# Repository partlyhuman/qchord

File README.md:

# Suzuki QChord Projects

Things that work with the Suzuki QChord, primarily a reproduction QCard that can be built with completely off-the-shelf parts. These projects are under active development.

# Physical devices

## [Q-Card Multicart QMC-001](pcbs/qcard-multicart)

You can get one as long as stock lasts <a href="https://ko-fi.com/s/ca15ec594a">at my Ko-Fi shop!</a>
<br>

A single cartridge that contains the entire Q-Card library, selectable by dip switches. The flash should be programmed prior to assembly, by concatenating the 4Mbit dumps you can find on archive.org.

## [Single Q-Card Reproduction](pcbs/qcard-single)

A rewriteable reproduction QCard PCB using SMD components. The flash module uses a TSOP32 package. It can be reprogrammed after assembly with the programmer adapter below.

# [Documentation](docs/)

Including 

* my research notes on the Q-Card hardware & connector
* my reverse-engineered Q-Card format
* continuing research into the sound bank present on Q-Chord

# [Software](software/)

Primarily, the `qcard` command-line tool that can be used to convert MIDI to and from Q-Cards.

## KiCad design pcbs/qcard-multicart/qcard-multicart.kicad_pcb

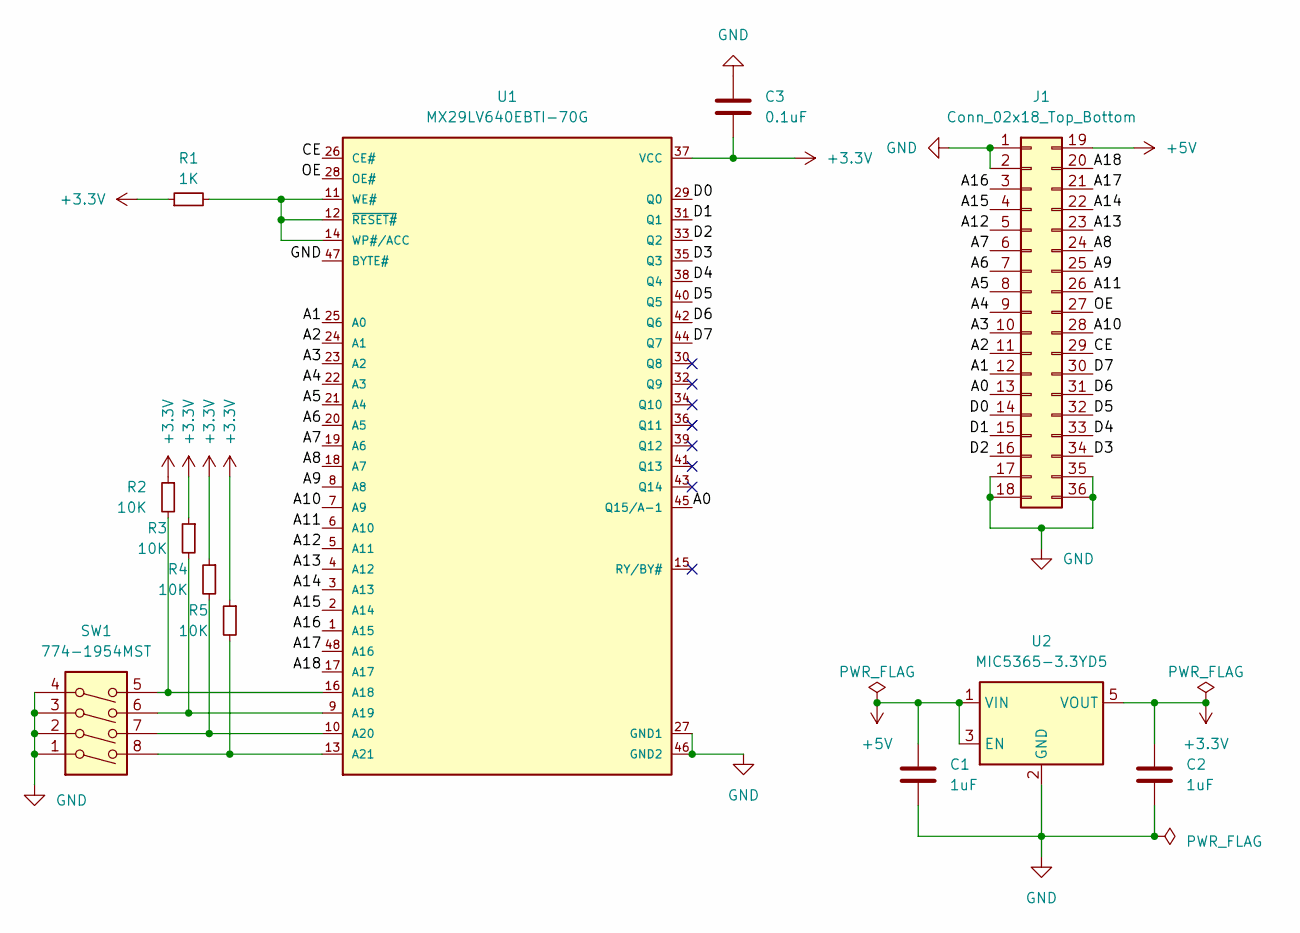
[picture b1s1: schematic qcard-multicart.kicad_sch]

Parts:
C1, C2: 1uF; C_0805_2012Metric_Pad1.18x1.45mm_HandSolder
C3: 0.1uF; C_0805_2012Metric_Pad1.18x1.45mm_HandSolder
J1: Conn_02x18_Top_Bottom; REB_EdgeConnector_36pin
R1: 1K; R_0805_2012Metric_Pad1.20x1.40mm_HandSolder
R2, R3, R4, R5: 10K; R_0805_2012Metric_Pad1.20x1.40mm_HandSolder
SW1: 774-1954MST; DIP-8_W7.62mm
U1: MX29LV640EBTI-70G; SOP50P2000X120-48N
U2: MIC5365-3.3YD5; SOT-23-5

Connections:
+3.3V: C2.1, C3.2, R1.1, R2.1, R3.1, R4.1, R5.1, U1.37 (VCC), U2.5 (VOUT)
+5V: C1.1, J1.19, U2.1 (VIN), U2.3 (EN)
/A0: J1.13, U1.45 (Q15/A-1)
/A1: J1.12, U1.25 (A0)
/A2: J1.11, U1.24 (A1)
/A3: J1.10, U1.23 (A2)
/A4: J1.9, U1.22 (A3)
/A5: J1.8, U1.21 (A4)
/A6: J1.7, U1.20 (A5)
/A7: J1.6, U1.19 (A6)
/A8: J1.24, U1.18 (A7)
/A9: J1.25, U1.8 (A8)
/A10: J1.28, U1.7 (A9)
/A11: J1.26, U1.6 (A10)
/A12: J1.5, U1.5 (A11)
/A13: J1.23, U1.4 (A12)
/A14: J1.22, U1.3 (A13)
/A15: J1.4, U1.2 (A14)
/A16: J1.3, U1.1 (A15)
/A17: J1.21, U1.48 (A16)
/A18: J1.20, U1.17 (A17)
/CE: J1.29, U1.26 (CE#)
/D0: J1.14, U1.29 (Q0)
/D1: J1.15, U1.31 (Q1)
/D2: J1.16, U1.33 (Q2)
/D3: J1.34, U1.35 (Q3)
/D4: J1.33, U1.38 (Q4)
/D5: J1.32, U1.40 (Q5)
/D6: J1.31, U1.42 (Q6)
/D7: J1.30, U1.44 (Q7)
/OE: J1.27, U1.28 (OE#)
GND: C1.2, C2.2, C3.1, J1.1, J1.2, J1.17, J1.18, J1.35, J1.36, SW1.1, SW1.2, SW1.3, SW1.4, U1.27 (GND1), U1.46 (GND2), U1.47 (BYTE#), U2.2 (GND)
unnamed: R2.2, SW1.5, U1.16 (A18)
unnamed: R3.2, SW1.6, U1.9 (A19)
unnamed: R4.2, SW1.7, U1.10 (A20)
unnamed: R5.2, SW1.8, U1.13 (A21)
unnamed: R1.2, U1.11 (WE#), U1.12 (~RESET#), U1.14 (WP#/ACC)

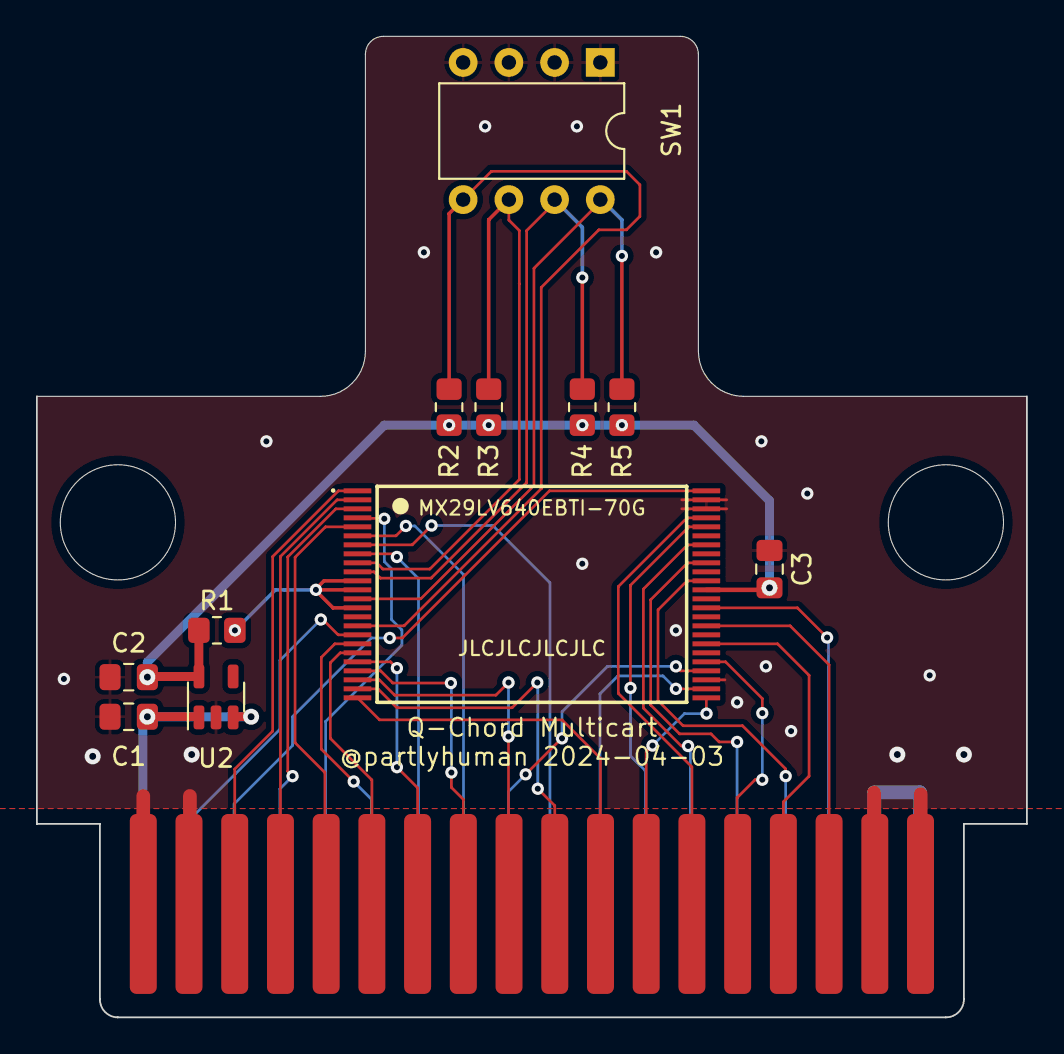
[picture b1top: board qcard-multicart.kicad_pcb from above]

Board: 2 copper layers, 55.0 x 54.5 mm, 14 parts (0 on the bottom side), 37 nets.

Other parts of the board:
H1, H2: MountingHole_6.4mm_M6

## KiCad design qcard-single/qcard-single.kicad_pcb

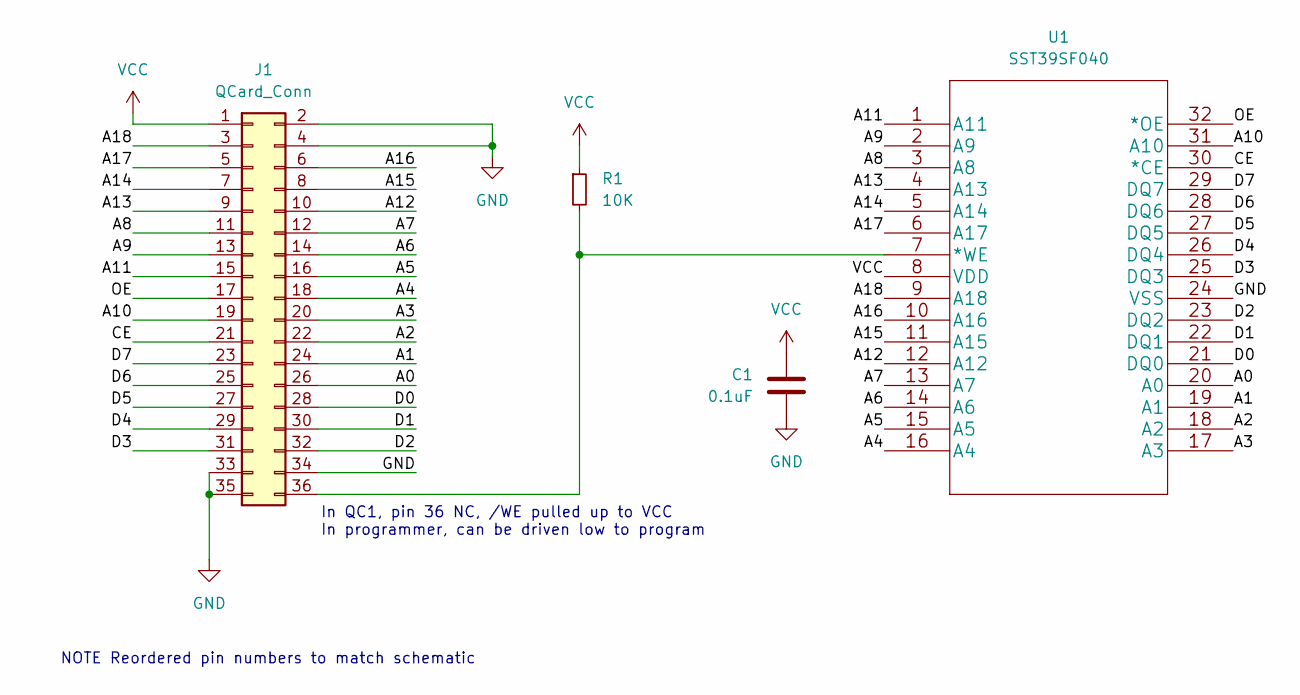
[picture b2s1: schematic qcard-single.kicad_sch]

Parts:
C1: 0.1uF; C_0805_2012Metric_Pad1.18x1.45mm_HandSolder
J1: QCard_Conn; REB_EdgeConnector_36pin
R1: 10K; R_0805_2012Metric_Pad1.20x1.40mm_HandSolder
U1: SST39SF040; SST39SF040-55-4C-WHE-T

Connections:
/A0: J1.26, U1.20 (A0)
/A1: J1.24, U1.19 (A1)
/A2: J1.22, U1.18 (A2)
/A3: J1.20, U1.17 (A3)
/A4: J1.18, U1.16 (A4)
/A5: J1.16, U1.15 (A5)
/A6: J1.14, U1.14 (A6)
/A7: J1.12, U1.13 (A7)
/A8: J1.11, U1.3 (A8)
/A9: J1.13, U1.2 (A9)
/A10: J1.19, U1.31 (A10)
/A11: J1.15, U1.1 (A11)
/A12: J1.10, U1.12 (A12)
/A13: J1.9, U1.4 (A13)
/A14: J1.7, U1.5 (A14)
/A15: J1.8, U1.11 (A15)
/A16: J1.6, U1.10 (A16)
/A17: J1.5, U1.6 (A17)
/A18: J1.3, U1.9 (A18)
/CE: J1.21, U1.30 (*CE)
/D0: J1.28, U1.21 (DQ0)
/D1: J1.30, U1.22 (DQ1)
/D2: J1.32, U1.23 (DQ2)
/D3: J1.31, U1.25 (DQ3)
/D4: J1.29, U1.26 (DQ4)
/D5: J1.27, U1.27 (DQ5)
/D6: J1.25, U1.28 (DQ6)
/D7: J1.23, U1.29 (DQ7)
/OE: J1.17, U1.32 (*OE)
GND: C1.1, J1.2, J1.4, J1.33, J1.34, J1.35, U1.24 (VSS)
unnamed: J1.36, R1.2, U1.7 (*WE)
VCC: C1.2, J1.1, R1.1, U1.8 (VDD)

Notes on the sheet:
In QC1, pin 36 NC, /WE pulled up to VCC In programmer, can be driven low to program
NOTE Reordered pin numbers to match schematic

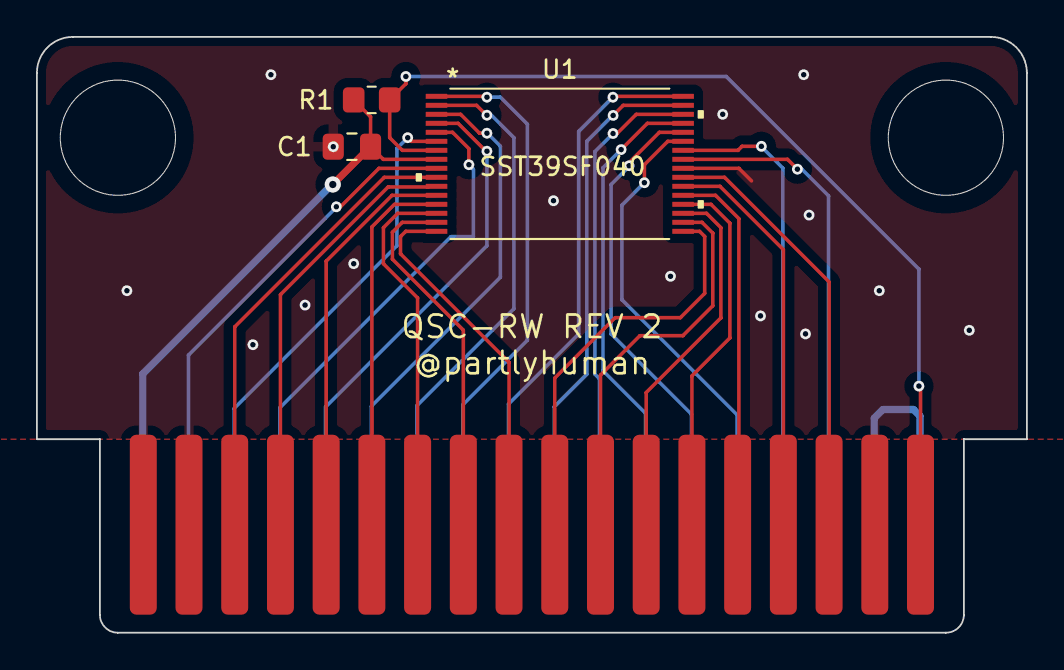
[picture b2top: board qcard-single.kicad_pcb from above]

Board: 4 copper layers, 55.0 x 33.1 mm, 6 parts (0 on the bottom side), 32 nets.

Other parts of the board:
H1, H2: MountingHole_6.4mm_M6

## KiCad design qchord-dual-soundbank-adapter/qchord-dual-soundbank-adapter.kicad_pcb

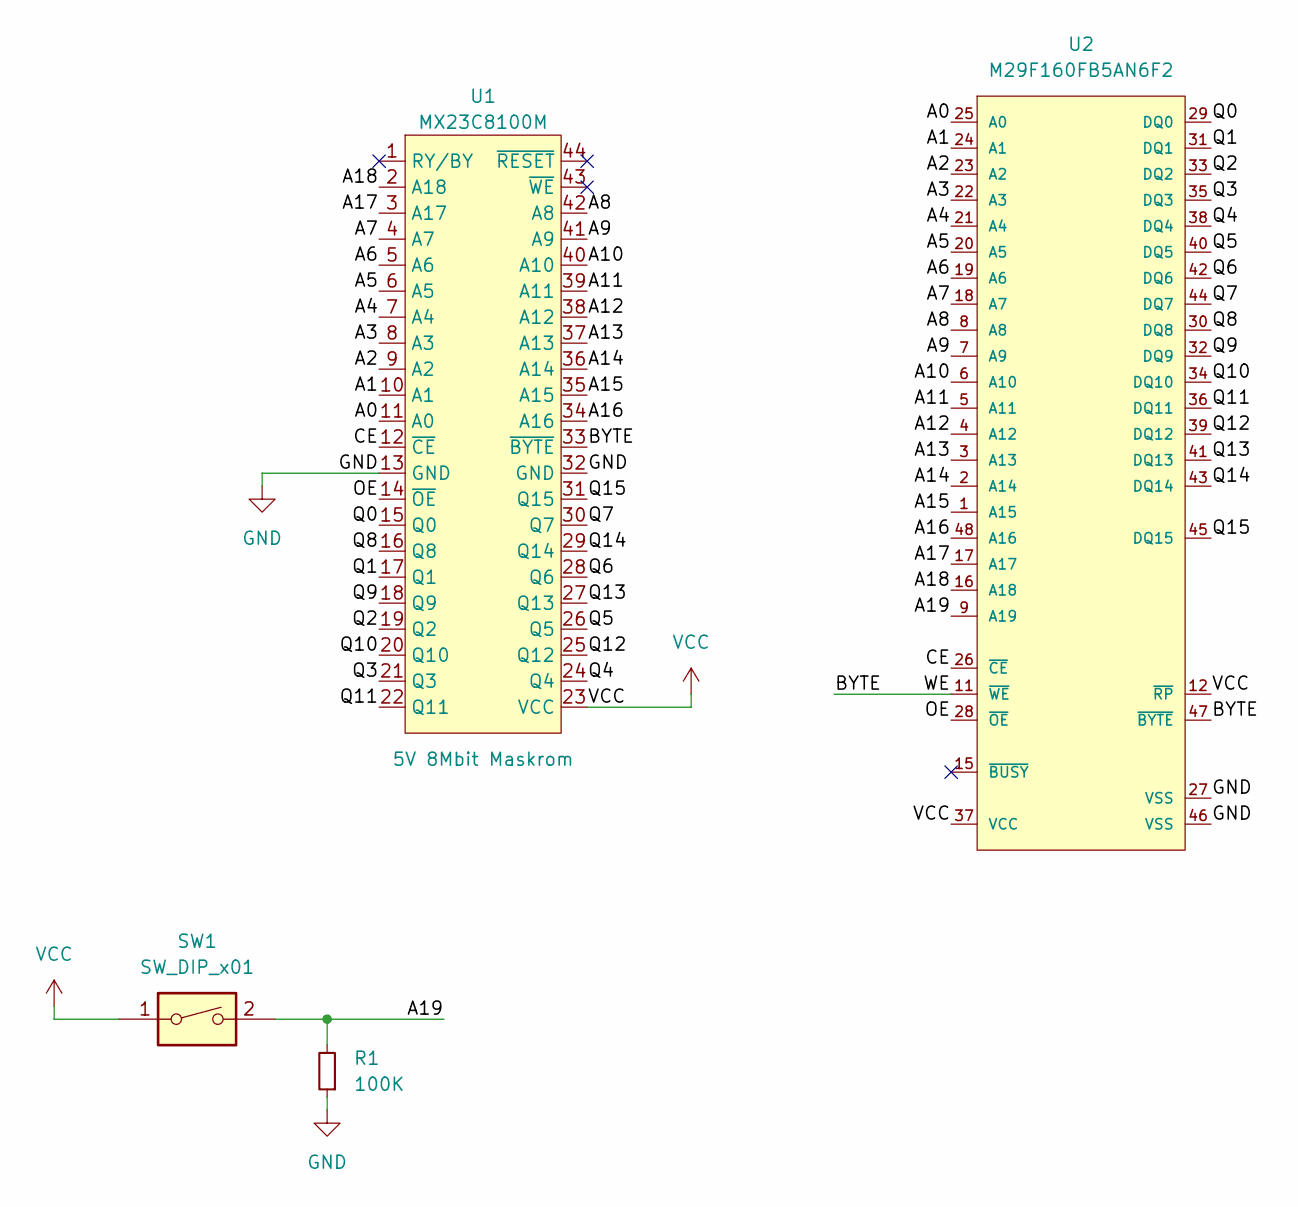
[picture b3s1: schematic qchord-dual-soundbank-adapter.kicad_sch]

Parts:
R1: 100K; R_0805_2012Metric_Pad1.20x1.40mm_HandSolder
SW1: SW_DIP_x01; SW_DIP_SPSTx01_Slide_9.78x4.72mm_W8.61mm_P2.54mm
U1: MX23C8100M; PSOP-44_Castellated
U2: M29F160FB5AN6F2; Micron-M29F160FB5AN6F2-Manufacturer_Recommended; Voltage 4.5V-5.5VÂ; Part Family M29FÂ

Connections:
/A0: U1.11 (A0), U2.25 (A0)
/A1: U1.10 (A1), U2.24 (A1)
/A2: U1.9 (A2), U2.23 (A2)
/A3: U1.8 (A3), U2.22 (A3)
/A4: U1.7 (A4), U2.21 (A4)
/A5: U1.6 (A5), U2.20 (A5)
/A6: U1.5 (A6), U2.19 (A6)
/A7: U1.4 (A7), U2.18 (A7)
/A8: U1.42 (A8), U2.8 (A8)
/A9: U1.41 (A9), U2.7 (A9)
/A10: U1.40 (A10), U2.6 (A10)
/A11: U1.39 (A11), U2.5 (A11)
/A12: U1.38 (A12), U2.4 (A12)
/A13: U1.37 (A13), U2.3 (A13)
/A14: U1.36 (A14), U2.2 (A14)
/A15: U1.35 (A15), U2.1 (A15)
/A16: U1.34 (A16), U2.48 (A16)
/A17: U1.3 (A17), U2.17 (A17)
/A18: U1.2 (A18), U2.16 (A18)
/A19: R1.2, SW1.2, U2.9 (A19)
/BYTE: U1.33 (~BYTE), U2.11 (~WE), U2.47 (~BYTE)
/CE: U1.12 (~CE), U2.26 (~CE)
/OE: U1.14 (~OE), U2.28 (~OE)
/Q0: U1.15 (Q0), U2.29 (DQ0)
/Q1: U1.17 (Q1), U2.31 (DQ1)
/Q2: U1.19 (Q2), U2.33 (DQ2)
/Q3: U1.21 (Q3), U2.35 (DQ3)
/Q4: U1.24 (Q4), U2.38 (DQ4)
/Q5: U1.26 (Q5), U2.40 (DQ5)
/Q6: U1.28 (Q6), U2.42 (DQ6)
/Q7: U1.30 (Q7), U2.44 (DQ7)
/Q8: U1.16 (Q8), U2.30 (DQ8)
/Q9: U1.18 (Q9), U2.32 (DQ9)
/Q10: U1.20 (Q10), U2.34 (DQ10)
/Q11: U1.22 (Q11), U2.36 (DQ11)
/Q12: U1.25 (Q12), U2.39 (DQ12)
/Q13: U1.27 (Q13), U2.41 (DQ13)
/Q14: U1.29 (Q14), U2.43 (DQ14)
/Q15: U1.31 (Q15), U2.45 (DQ15)
GND: R1.1, U1.13 (GND), U1.32 (GND), U2.27 (VSS), U2.46 (VSS)
VCC: SW1.1, U1.23 (VCC), U2.12 (~RP), U2.37 (VCC)

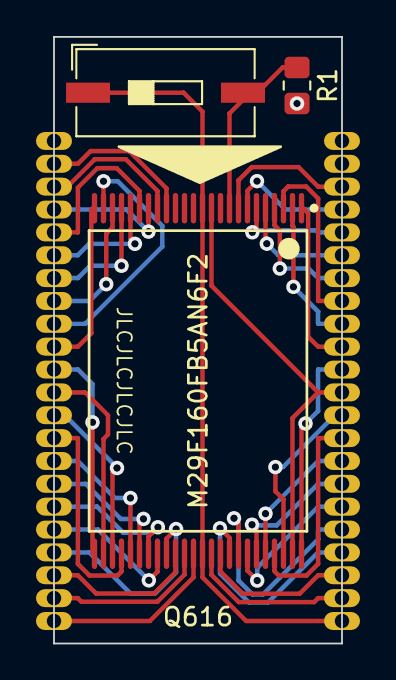
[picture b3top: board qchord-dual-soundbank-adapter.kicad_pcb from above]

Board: 2 copper layers, 16.0 x 33.7 mm, 4 parts (0 on the bottom side), 41 nets.

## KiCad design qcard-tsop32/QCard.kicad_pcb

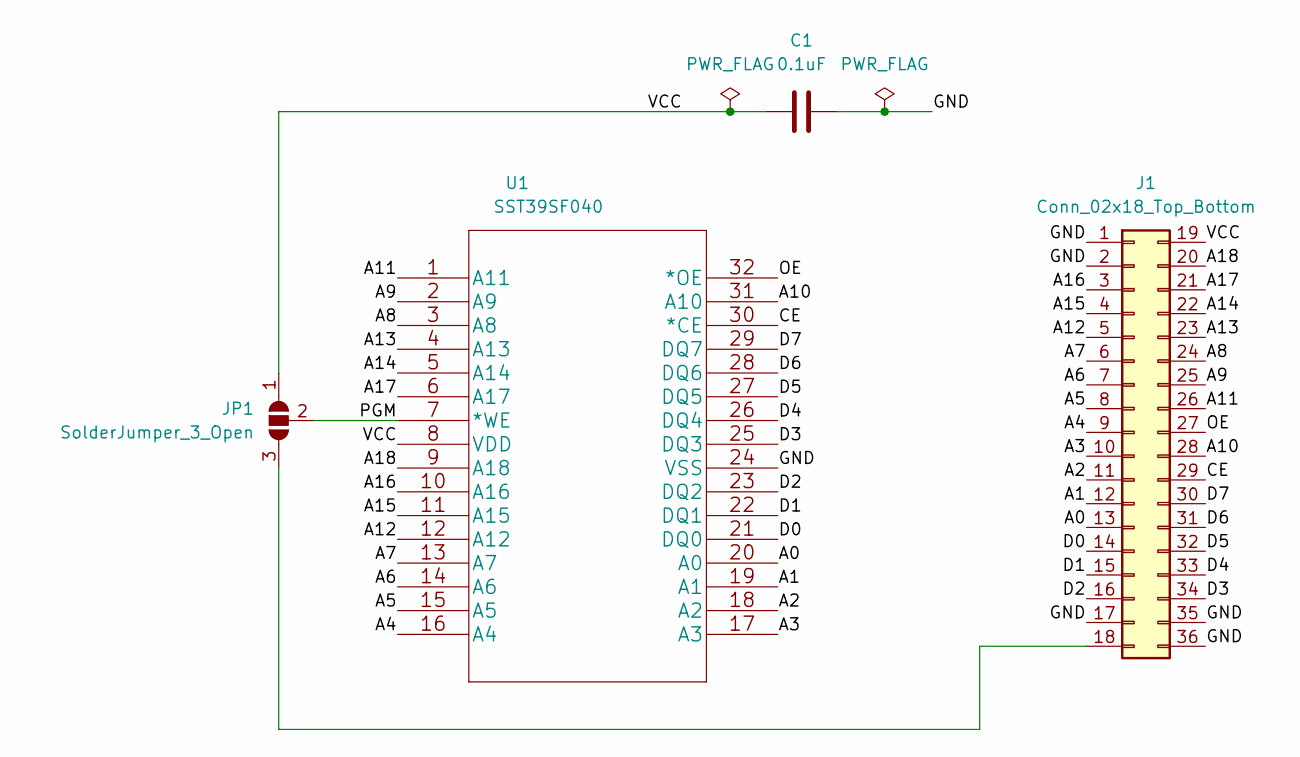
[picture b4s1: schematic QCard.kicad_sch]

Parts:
C1: 0.1uF; C_0805_2012Metric_Pad1.18x1.45mm_HandSolder
J1: Conn_02x18_Top_Bottom; REB_EdgeConnector_36pin
JP1: SolderJumper_3_Open; SolderJumper-3_P1.3mm_Open_Pad1.0x1.5mm
U1: SST39SF040; SST39SF040-55-4C-WHE-T

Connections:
/A0: J1.13, U1.20 (A0)
/A1: J1.12, U1.19 (A1)
/A2: J1.11, U1.18 (A2)
/A3: J1.10, U1.17 (A3)
/A4: J1.9, U1.16 (A4)
/A5: J1.8, U1.15 (A5)
/A6: J1.7, U1.14 (A6)
/A7: J1.6, U1.13 (A7)
/A8: J1.24, U1.3 (A8)
/A9: J1.25, U1.2 (A9)
/A10: J1.28, U1.31 (A10)
/A11: J1.26, U1.1 (A11)
/A12: J1.5, U1.12 (A12)
/A13: J1.23, U1.4 (A13)
/A14: J1.22, U1.5 (A14)
/A15: J1.4, U1.11 (A15)
/A16: J1.3, U1.10 (A16)
/A17: J1.21, U1.6 (A17)
/A18: J1.20, U1.9 (A18)
/CE: J1.29, U1.30 (*CE)
/D0: J1.14, U1.21 (DQ0)
/D1: J1.15, U1.22 (DQ1)
/D2: J1.16, U1.23 (DQ2)
/D3: J1.34, U1.25 (DQ3)
/D4: J1.33, U1.26 (DQ4)
/D5: J1.32, U1.27 (DQ5)
/D6: J1.31, U1.28 (DQ6)
/D7: J1.30, U1.29 (DQ7)
/GND: C1.2, J1.1, J1.2, J1.17, J1.35, J1.36, U1.24 (VSS)
/OE: J1.27, U1.32 (*OE)
/PGM: JP1.2 (C), U1.7 (*WE)
/VCC: C1.1, J1.19, JP1.1 (A), U1.8 (VDD)
unnamed: J1.18, JP1.3 (B)

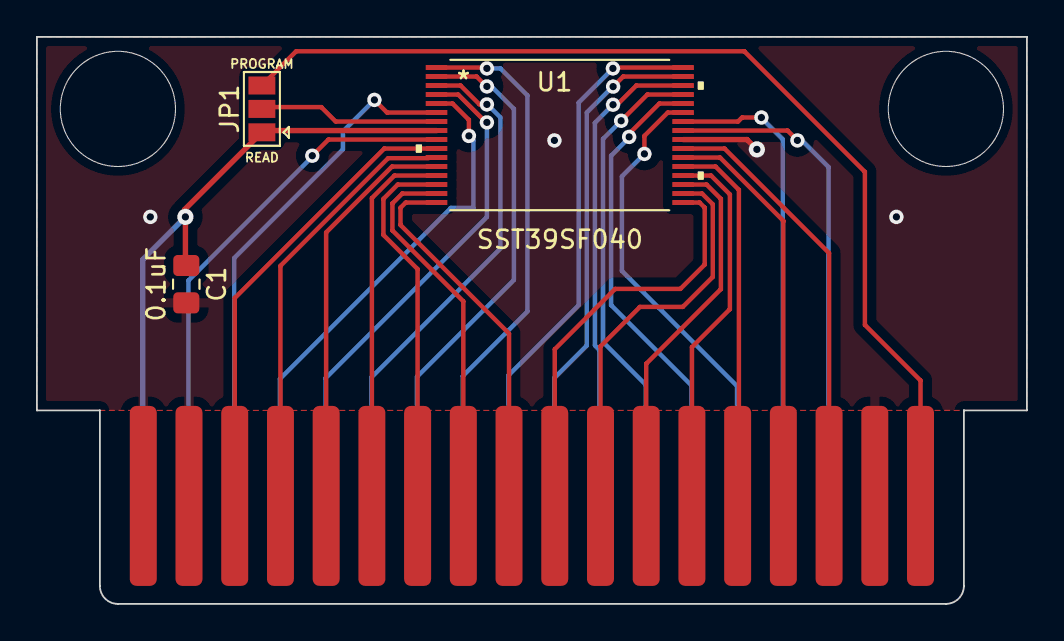
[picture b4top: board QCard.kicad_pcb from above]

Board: 2 copper layers, 55.0 x 31.5 mm, 4 parts (0 on the bottom side), 33 nets.

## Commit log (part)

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2022-12-29 Adds dumps, only direct ones are accurate, two address pins tied together
2022-12-29 Add dumper PCB v0
2023-01-02 Dumper v1
2023-01-15 update ignores
2023-01-15 TSOP32 flash cart v0
2023-01-15 Adds jumper for programming, fixes all DRC errors but loses mounting holes
2023-01-15 Restores mounting holes
2023-01-15 Adds label
2023-01-15 Nudge mounting holes
2023-01-15 Remove intermediate directory
2023-01-16 Better write protect jumper behaviour, using text vars
2023-01-16 Solve ERC warnings
2023-01-18 Adds properly dumped cards
2023-01-19 Pulling WE high for reading per datasheet
2023-01-19 Center silkscreen
2023-01-24 Better labeling
2023-01-24 update date
2023-01-24 Completing dumps
2023-01-24 Splitting QSC2/3
2023-01-24 Committing doubled binaries
2023-01-25 Adds printable case (for standard size Q-card, not minimized one)
2023-01-25 Adds programmer pcb
2023-01-26 Extra grounding and better silkscreen positioning on smaller pcb
2023-02-08 Removed
2023-02-08 New case design for smaller PCB
2023-02-08 Adds readme
2023-02-08 Adds images to docs
2023-02-08 Adds MIT license
2023-02-13 Multicart design sketch
2023-02-14 First pass at multicart
2023-02-14 Maybe usable prototype
2023-02-14 changing pulldown to pullup
2023-03-14 I actually don't know what the difference here is
2023-03-15 Multicart: connect OE/CE instead of always on, solve some DRC violations
2023-03-15 Multicart: adds missing 3d parts
2023-03-15 Adding 4mm clearance to switches
2023-03-15 Adding another 4mm clearance, cutting out dead board
2023-03-21 Refactor multicart to use SMD resistor array for ease of assembly
2023-04-02 Adds multicart case 3d print
2023-04-02 Update screenshot
2023-05-23 Adding Q-Chord schematic because I keep losing it
2023-05-23 Dumping Q-Chord program ROM
2023-05-24 Dump soundbank
2023-05-24 Investigation of sound bank
2023-05-24 Diff in subsequent dump?
2023-05-24 Adds board adapting SOP44 maskrom to TSOP48 flash
2023-05-24 Consolidate .gitignores
2023-05-24 Replacing bad dump
2023-05-24 Flip outtie to innie
2023-05-24 Makes room for neighboring IC
2023-05-25 Further investigation into soundfont format
2023-05-25 Adds playable wavs
2023-05-25 Further findings
2023-05-31 Adds sam9407 tools and docs
2023-06-06 Comic sans to match mainboard
2023-06-06 Redesign in-place
2023-06-07 Don't leave stuff floating
2023-06-07 Adding doc
2023-06-07 add extra GND
2023-06-09 Adds some docs, pre-reversed Q616 dump
2023-09-03 Adds datasheet & notes
2023-09-03 Adds notes
2023-09-03 More notes
2023-09-29 Dual soundbank adapter
2023-11-09 Add 80C51 MPU datasheets
2023-11-09 Potentially useful tool from Dream.fr
2023-11-09 pullup instead of pulldown by default
2023-11-11 Dumping GMD970800 from Terratec Pro Media WT64
2023-11-11 clarify datasheets
2023-11-11 more renames
2023-11-18 soundbank research
2023-12-13 Removes resistor pack, current limits pulled up inputs
2024-01-13 Adds staggered RNs (painstakingly)
2024-01-13 Move all components to front
2024-01-13 Production ready files
2024-04-04 Space out components for easier hand soldering
2024-04-14 New render
2024-06-05 Update README.md - BOMs were outdated
2024-06-06 Updating case print, moving thread so little bit doesn't snap off
2024-06-06 Create project for SAM9713 dev board
2024-08-28 Uncovering SAM tools
2024-08-28 Remove devboard not really in use
2024-08-28 Users manual
2024-08-29 Yesssss
2024-08-29 Table formatting
2024-08-31 Removing older working files
2024-08-31 Extracted SNDEDIT tools from self-installer
2024-09-08 Instrument tables
2024-09-08 Parse instrument splits
2024-09-08 WIP, about to change to streams
2024-09-11 Add japanese user manual
2024-09-12 Converter
2024-09-12 QCard->Midi progress
2024-09-13 Fixed problemo
2024-09-13 Remove debugging
2024-09-13 Tidying
2024-09-13 Discovered Read*BigEndian methods
2024-09-13 Cleanup midi event categories
2024-09-13 More tostring
2024-09-13 Muting B0 and AA events makes only diff the extra pitch bends that were captured and system reset after song end
2024-09-13 MIDI out
2024-09-13 Found new magic number at 0x10
2024-09-13 Adjust tempo
2024-09-14 Tempo calculation assuming 120bpm
2024-09-14 Export all tracks
2024-09-14 Use tempo event and fixed tickdiv
2024-09-14 Adds time signature meta
2024-09-14 Fixes to time sig
2024-09-14 Random pointless little changes
2024-09-14 Refactor solution
2024-09-14 Generate qcard from raw
2024-09-15 Stubbing out midi-to-qcard conversion but using incorrect midi event consumption
2024-09-15 Encapsulate warnings, reorg consolidating chunk code
2024-09-15 Continuing midi parsing
2024-09-15 Passing roundtrip test
2024-09-15 Debugging output, truncating full card
2024-09-15 Parse tempo
2024-09-16 Fixes variable length encoding
2024-09-16 Chop out verbose logging
2024-09-16 Adds tests
2024-09-16 Scaling dt when tickdiv differs in MIDI
2024-09-17 Add qcard documentation
2024-09-17 Add picture
2024-09-17 Better checking for track ranges
2024-09-17 More static imports for conciseness
2024-09-17 Refactor Qcard->MIDI into QCardMidiTrack, add indexer to QCard
2024-09-17 Cleanup and adding publish steps
2024-09-20 Trim garbage from end of raw tracks
2024-09-22 Revisiting single Qcard, renumber pins to match schematic
2024-09-22 Document cart edge
2024-09-22 Replace qcard-tsop32
2024-09-23 Initializing qcard memory to FFs for quicker flashing
2024-09-23 Adding to documentation
2024-09-23 Cleanups, eliminate extra copy instantiating QcardMidiTrack
2024-09-23 Use resizable memory buffers instead of guessing size
2024-09-23 Add fake key meta
2024-09-24 Don't write out specials into MIDI, they're not valid
2024-09-24 Quick and dirty metronome track generation
2024-11-01 WIP merging into single multitool
2024-11-07 Consolidates add metronome tool, cleans up warnings
2024-11-08 First draft of tabs parser
2024-11-08 Output midi events in hex
2024-11-08 Distinguish between lyrics and tab lines
2024-11-10 WIP pairs
2024-11-10 Fix multi-instance -i1 -o2
2024-11-10 Swizzling tracks
2024-11-13 Rearranging some stuff in the commandline
2024-11-13 Such minor
2024-12-27 Gives 0.5mm extra tolerance to case, wasn't closing well
2024-12-29 Minor fitment tweaks to multicart case
2025-03-07 Reorg
2025-08-22 Update print with no support holes
2025-12-09 Update multicart case to have tighter fit

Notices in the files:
parts and their libraries:
Copyright 2021 Accelerated Designs. All rights reserved.
